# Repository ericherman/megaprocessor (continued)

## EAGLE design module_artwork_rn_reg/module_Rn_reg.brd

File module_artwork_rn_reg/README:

Rn Registers

This is where the General Purpose Registers (R0, R1, R2, R3) live. They
can be written to from various places.

Usually at most one register is written to in a cycle. However during
MUL and DIV upto all 4 may be written to in a cycle. In this mode each
register has its own shifter to generate its required new value.

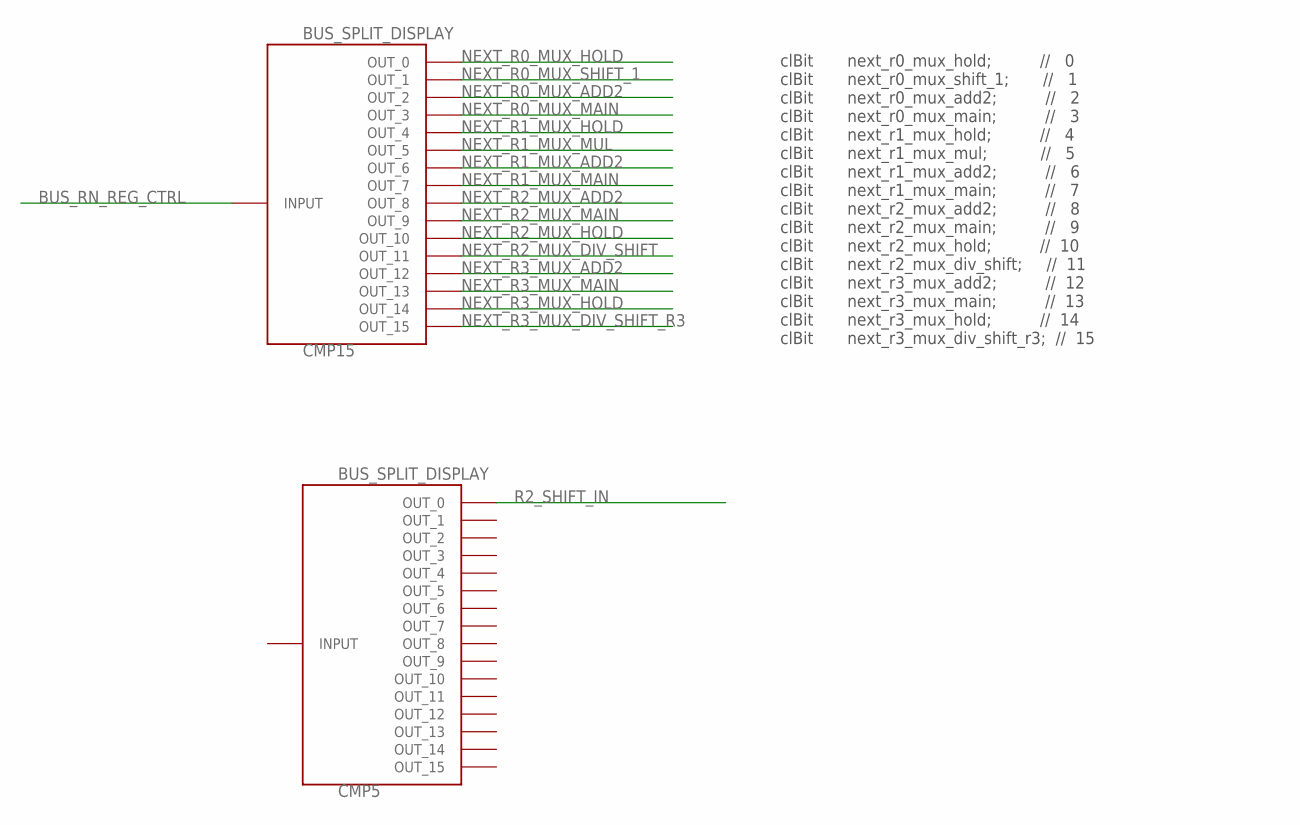
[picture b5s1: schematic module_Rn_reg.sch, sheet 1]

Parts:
CMP5, CMP15: BUS_SPLIT_DISPLAY

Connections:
BUS_RN_REG_CTRL: CMP15.INPUT
NEXT_R0_MUX_ADD2: CMP15.P$3 (OUT_2); also elsewhere on the board
NEXT_R0_MUX_HOLD: CMP15.P$1 (OUT_0); also elsewhere on the board
NEXT_R0_MUX_MAIN: CMP15.P$4 (OUT_3); also elsewhere on the board
NEXT_R0_MUX_SHIFT_1: CMP15.P$2 (OUT_1); also elsewhere on the board
NEXT_R1_MUX_ADD2: CMP15.P$7 (OUT_6); also elsewhere on the board
NEXT_R1_MUX_HOLD: CMP15.P$5 (OUT_4); also elsewhere on the board
NEXT_R1_MUX_MAIN: CMP15.P$8 (OUT_7); also elsewhere on the board
NEXT_R1_MUX_MUL: CMP15.P$6 (OUT_5); also elsewhere on the board
NEXT_R2_MUX_ADD2: CMP15.P$9 (OUT_8); also elsewhere on the board
NEXT_R2_MUX_DIV_SHIFT: CMP15.P$12 (OUT_11); also elsewhere on the board
NEXT_R2_MUX_HOLD: CMP15.P$11 (OUT_10); also elsewhere on the board
NEXT_R2_MUX_MAIN: CMP15.P$10 (OUT_9); also elsewhere on the board
NEXT_R3_MUX_ADD2: CMP15.P$13 (OUT_12); also elsewhere on the board
NEXT_R3_MUX_DIV_SHIFT_R3: CMP15.P$16 (OUT_15); also elsewhere on the board
NEXT_R3_MUX_HOLD: CMP15.P$15 (OUT_14); also elsewhere on the board
NEXT_R3_MUX_MAIN: CMP15.P$14 (OUT_13); also elsewhere on the board
R2_SHIFT_IN: CMP5.P$1 (OUT_0); also elsewhere on the board

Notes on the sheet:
clBit next_r0_mux_hold; // 0 clBit next_r0_mux_shift_1; // 1 clBit next_r0_mux_add2; // 2 clBit next_r0_mux_main; // 3 clBit next_r1_mux_hold; // 4 clBit next_r1_mux_mul; // 5 clBit next_r1_mux_add2; // 6 clBit next_r1_mux_main; // 7 clBit next_r2_mux_add2; // 8 clBit next_r2_mux_main; // 9 clBit n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

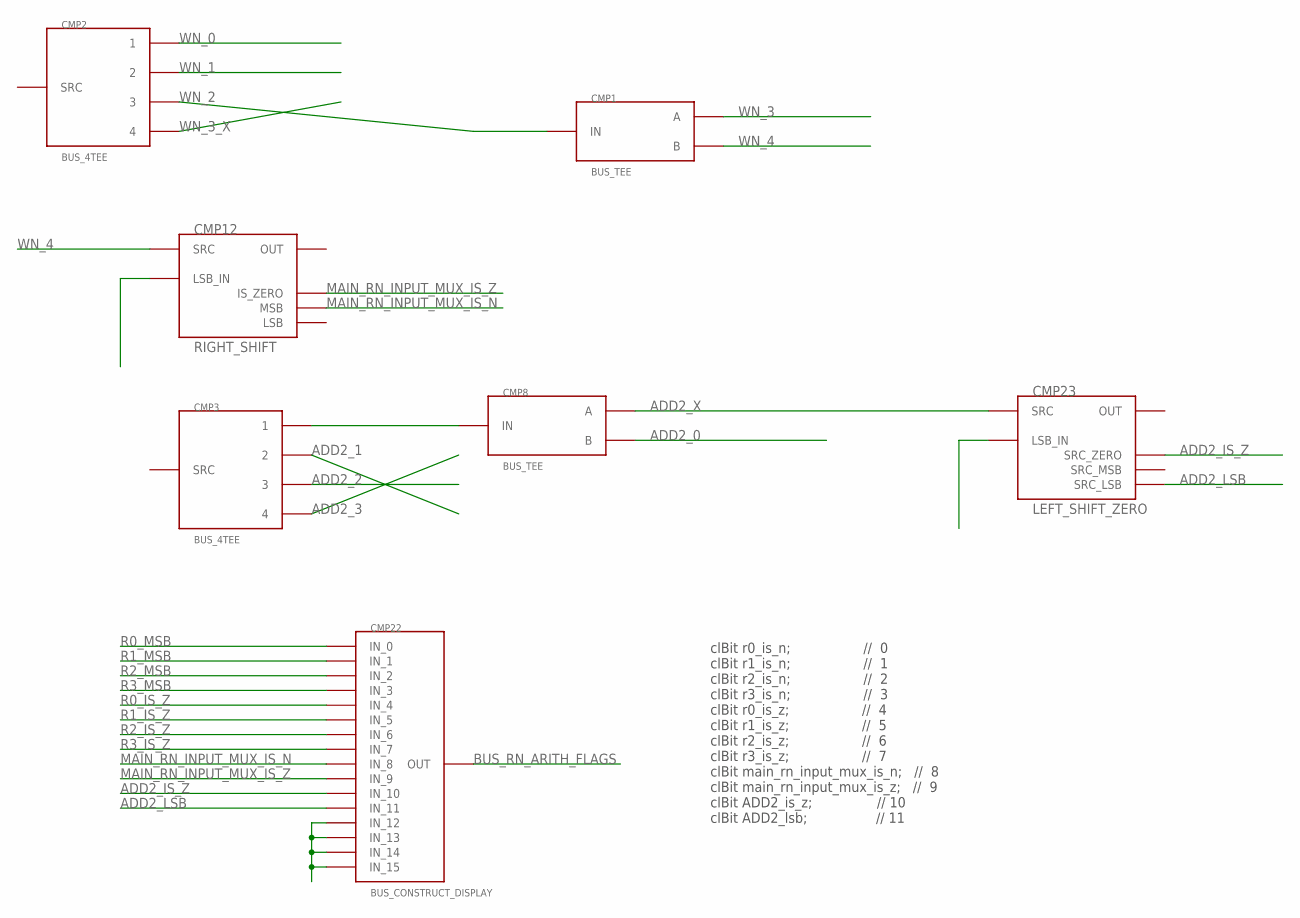
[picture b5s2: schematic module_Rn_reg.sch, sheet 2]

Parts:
CMP1, CMP8: BUS_TEE
CMP2, CMP3: BUS_4TEE
CMP12: RIGHT_SHIFT; SHIFT_ZERO
CMP22: BUS_CONSTRUCT_DISPLAY; BUS_SPLIT_DISPLAY
CMP23: LEFT_SHIFT_ZERO; SHIFT_ZERO

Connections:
ADD2_0: CMP8.OUTB (B); also elsewhere on the board
ADD2_1: CMP3.4; also elsewhere on the board
ADD2_2: CMP3.3; also elsewhere on the board
ADD2_3: CMP3.2; also elsewhere on the board
ADD2_IS_Z: CMP22.P$11 (IN_10), CMP23.IS_ZERO (SRC_ZERO)
ADD2_LSB: CMP22.P$12 (IN_11), CMP23.LSB (SRC_LSB)
ADD2_X: CMP8.OUT_A (A), CMP23.LSRC (SRC)
BUS_RN_ARITH_FLAGS: CMP22.INPUT (OUT)
MAIN_RN_INPUT_MUX_IS_N: CMP12.MSB, CMP22.P$9 (IN_8)
MAIN_RN_INPUT_MUX_IS_Z: CMP12.IS_ZERO, CMP22.P$10 (IN_9)
unnamed: CMP22.P$13 (IN_12), CMP22.P$14 (IN_13), CMP22.P$15 (IN_14), CMP22.P$16 (IN_15)
unnamed: CMP3.1, CMP8.INPUT (IN)
R0_IS_Z: CMP22.P$5 (IN_4); also elsewhere on the board
R0_MSB: CMP22.P$1 (IN_0); also elsewhere on the board
R1_IS_Z: CMP22.P$6 (IN_5); also elsewhere on the board
R1_MSB: CMP22.P$2 (IN_1); also elsewhere on the board
R2_IS_Z: CMP22.P$7 (IN_6); also elsewhere on the board
R2_MSB: CMP22.P$3 (IN_2); also elsewhere on the board
R3_IS_Z: CMP22.P$8 (IN_7); also elsewhere on the board
R3_MSB: CMP22.P$4 (IN_3); also elsewhere on the board
WN_0: CMP2.1; also elsewhere on the board
WN_1: CMP2.2; also elsewhere on the board
WN_2: CMP2.4; also elsewhere on the board
WN_3: CMP1.OUT_A (A); also elsewhere on the board
WN_3_X: CMP1.INPUT (IN), CMP2.3
WN_4: CMP1.OUTB (B), CMP12.RSRC (SRC)

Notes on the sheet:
clBit r0_is_n; // 0 clBit r1_is_n; // 1 clBit r2_is_n; // 2 clBit r3_is_n; // 3 clBit r0_is_z; // 4 clBit r1_is_z; // 5 clBit r2_is_z; // 6 clBit r3_is_z; // 7 clBit main_rn_input_mux_is_n; // 8 clBit main_rn_input_mux_is_z; // 9 clBit ADD2_is_z; // 10 clBit ADD2_lsb; // 11

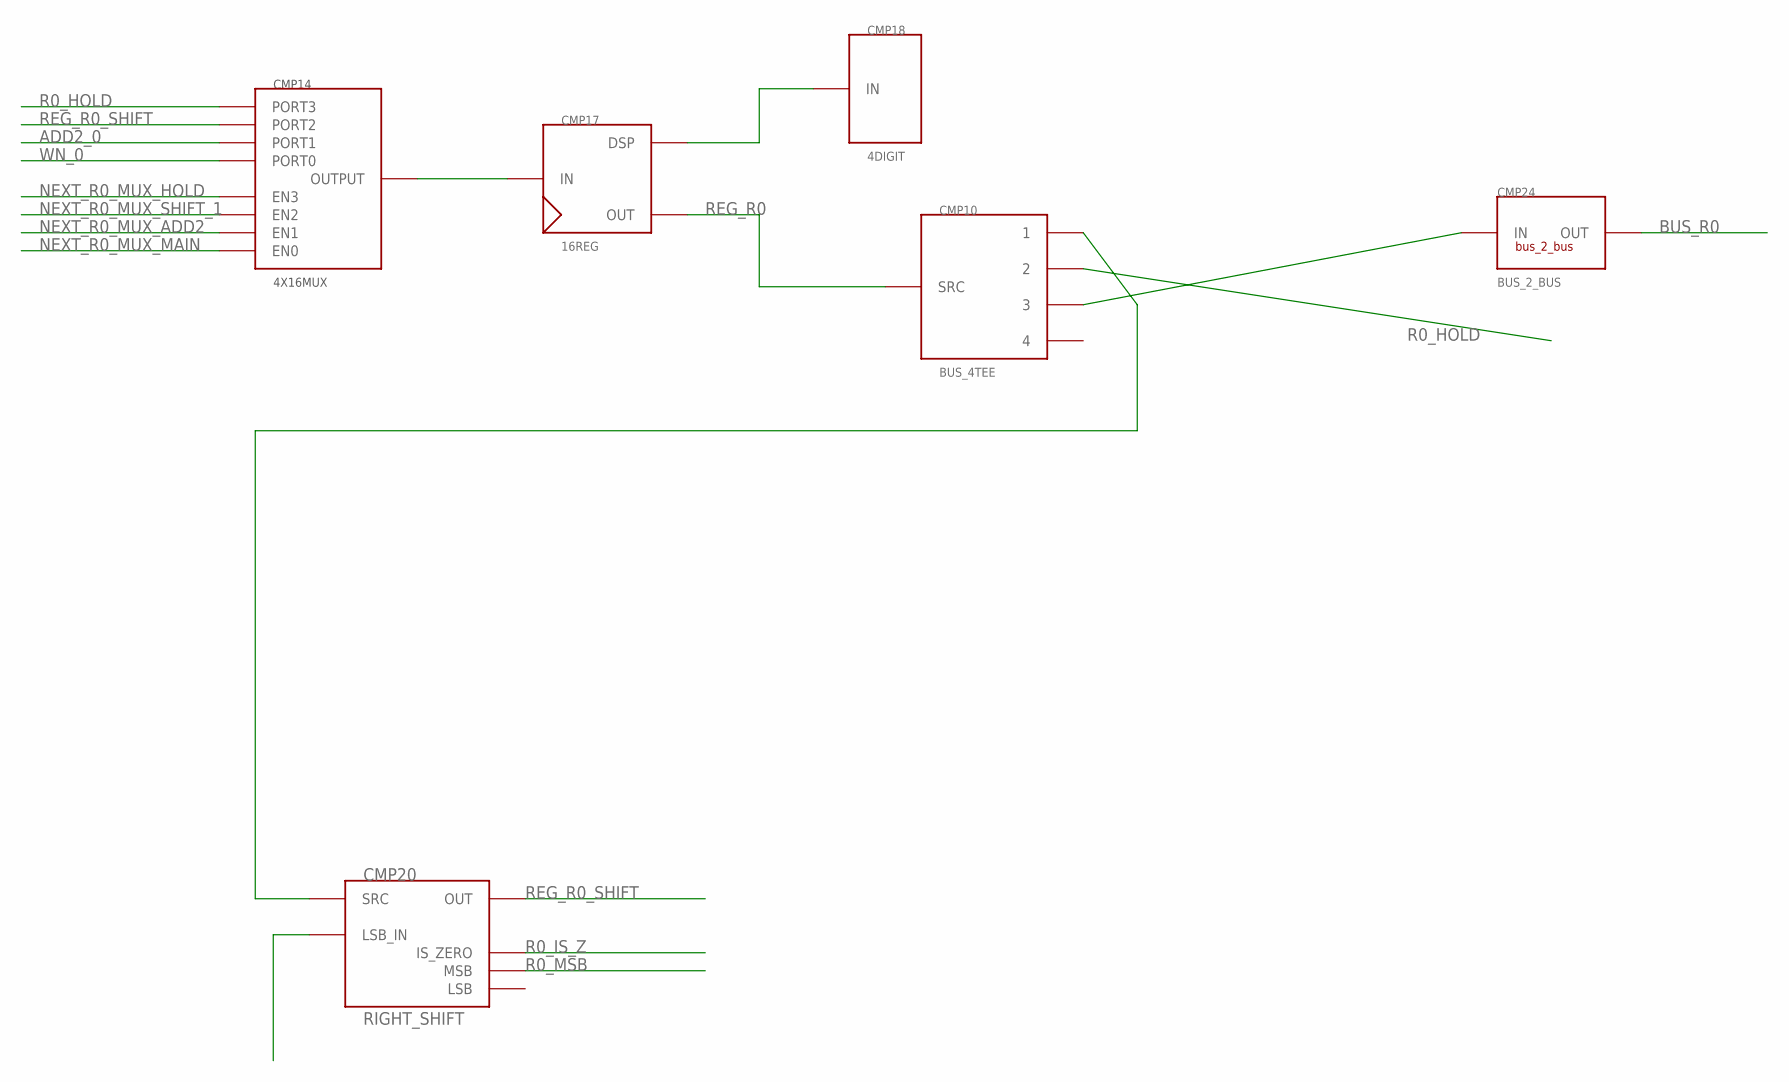
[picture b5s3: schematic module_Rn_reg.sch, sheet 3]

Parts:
CMP10: BUS_4TEE
CMP14: 4X16MUX
CMP17: 16REG
CMP18: 4DIGIT
CMP20: RIGHT_SHIFT; SHIFT_ZERO
CMP24: BUS_2_BUS; BUS2BUS

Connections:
ADD2_0: CMP14.PORT1; also elsewhere on the board
BUS_R0: CMP24.P$2 (OUT)
unnamed: CMP14.PORTOUT (OUTPUT), CMP17.INPUT (IN)
unnamed: CMP17.DISPLAY (DSP), CMP18.P$1
unnamed: CMP10.1, CMP20.RSRC (SRC)
unnamed: CMP10.3, CMP24.P$1 (IN)
NEXT_R0_MUX_ADD2: CMP14.EN1; also elsewhere on the board
NEXT_R0_MUX_HOLD: CMP14.EN3; also elsewhere on the board
NEXT_R0_MUX_MAIN: CMP14.EN0; also elsewhere on the board
NEXT_R0_MUX_SHIFT_1: CMP14.EN2; also elsewhere on the board
R0_HOLD: CMP10.2, CMP14.PORT3
R0_IS_Z: CMP20.IS_ZERO; also elsewhere on the board
R0_MSB: CMP20.MSB; also elsewhere on the board
REG_R0: CMP10.SRC, CMP17.OUT
REG_R0_SHIFT: CMP14.PORT2, CMP20.LSRC (OUT)
WN_0: CMP14.PORT0; also elsewhere on the board

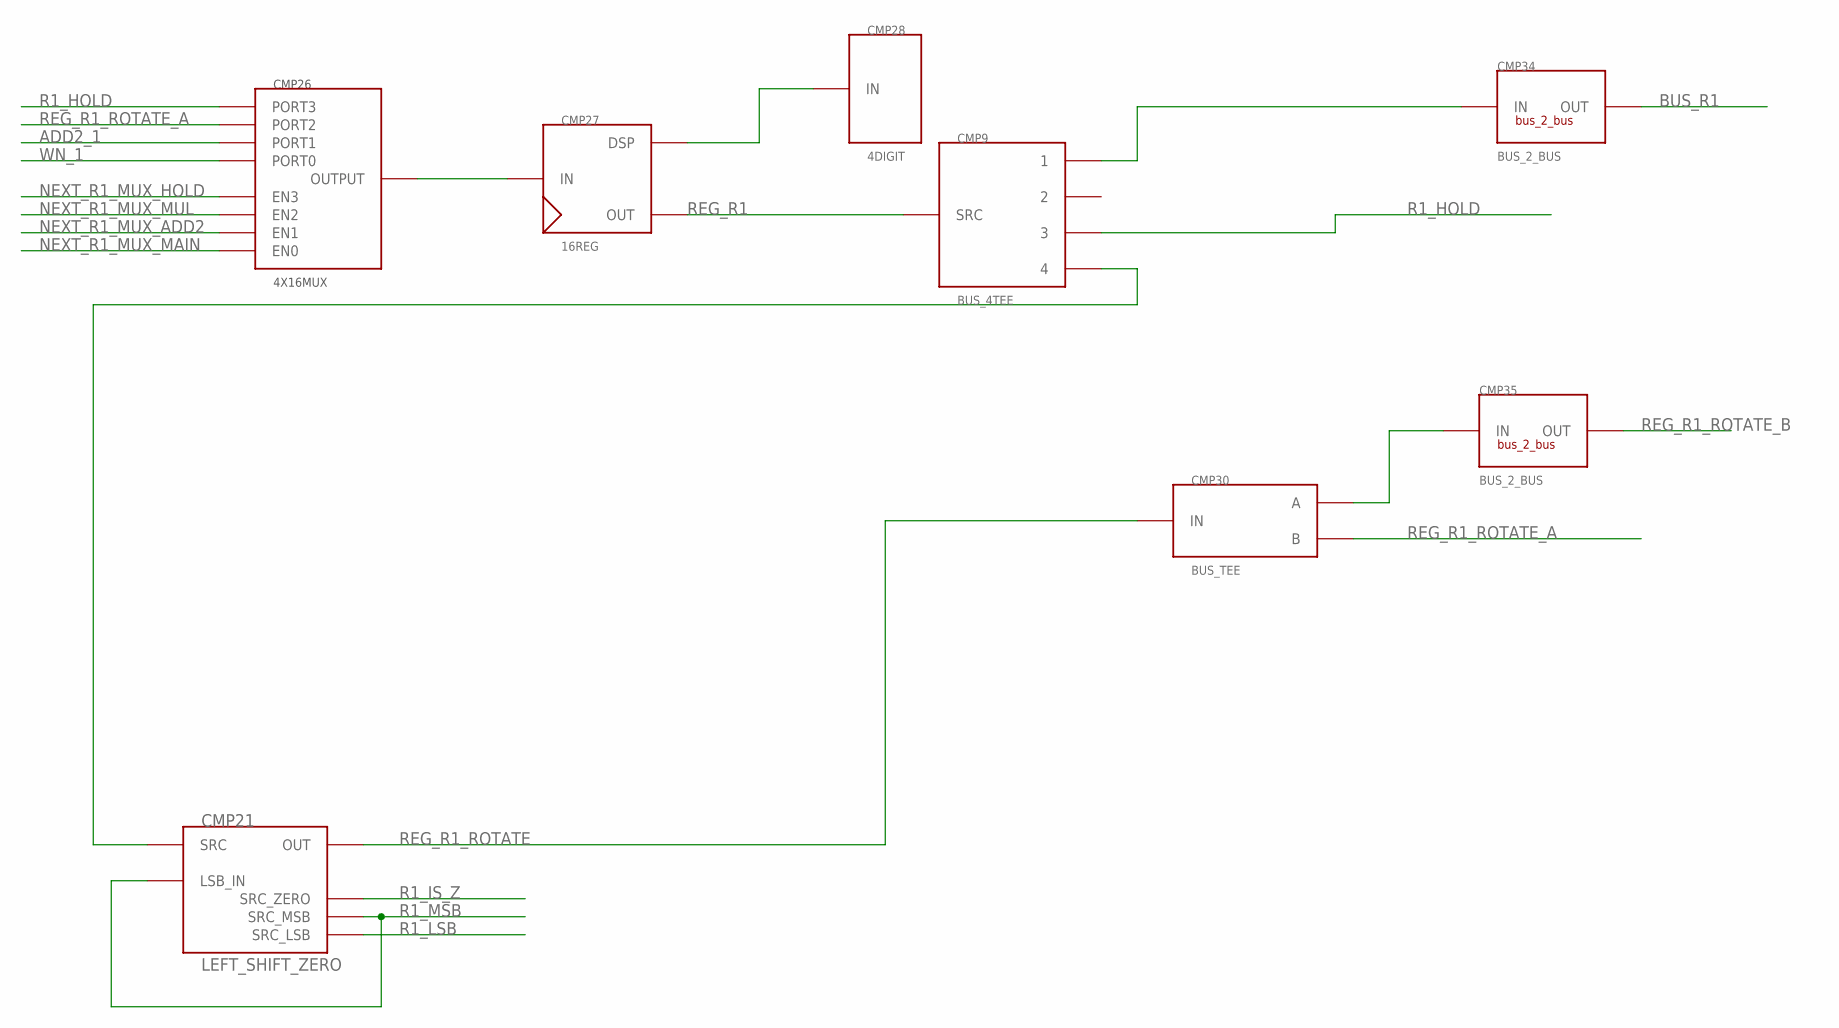
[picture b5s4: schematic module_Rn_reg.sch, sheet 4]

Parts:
CMP9: BUS_4TEE
CMP21: LEFT_SHIFT_ZERO; SHIFT_ZERO
CMP26: 4X16MUX
CMP27: 16REG
CMP28: 4DIGIT
CMP30: BUS_TEE
CMP34, CMP35: BUS_2_BUS; BUS2BUS

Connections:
ADD2_1: CMP26.PORT1; also elsewhere on the board
BUS_R1: CMP34.P$2 (OUT)
unnamed: CMP26.PORTOUT (OUTPUT), CMP27.INPUT (IN)
unnamed: CMP27.DISPLAY (DSP), CMP28.P$1
unnamed: CMP9.1, CMP34.P$1 (IN)
unnamed: CMP9.4, CMP21.LSRC (SRC)
unnamed: CMP30.OUT_A (A), CMP35.P$1 (IN)
NEXT_R1_MUX_ADD2: CMP26.EN1; also elsewhere on the board
NEXT_R1_MUX_HOLD: CMP26.EN3; also elsewhere on the board
NEXT_R1_MUX_MAIN: CMP26.EN0; also elsewhere on the board
NEXT_R1_MUX_MUL: CMP26.EN2; also elsewhere on the board
R1_HOLD: CMP9.3, CMP26.PORT3
R1_IS_Z: CMP21.IS_ZERO (SRC_ZERO); also elsewhere on the board
R1_LSB: CMP21.LSB (SRC_LSB)
R1_MSB: CMP21.MSB (SRC_MSB), CMP21.SHIFT_IN (LSB_IN); also elsewhere on the board
REG_R1: CMP9.SRC, CMP27.OUT
REG_R1_ROTATE: CMP21.RSRC (OUT), CMP30.INPUT (IN)
REG_R1_ROTATE_A: CMP26.PORT2, CMP30.OUTB (B)
REG_R1_ROTATE_B: CMP35.P$2 (OUT)
WN_1: CMP26.PORT0; also elsewhere on the board

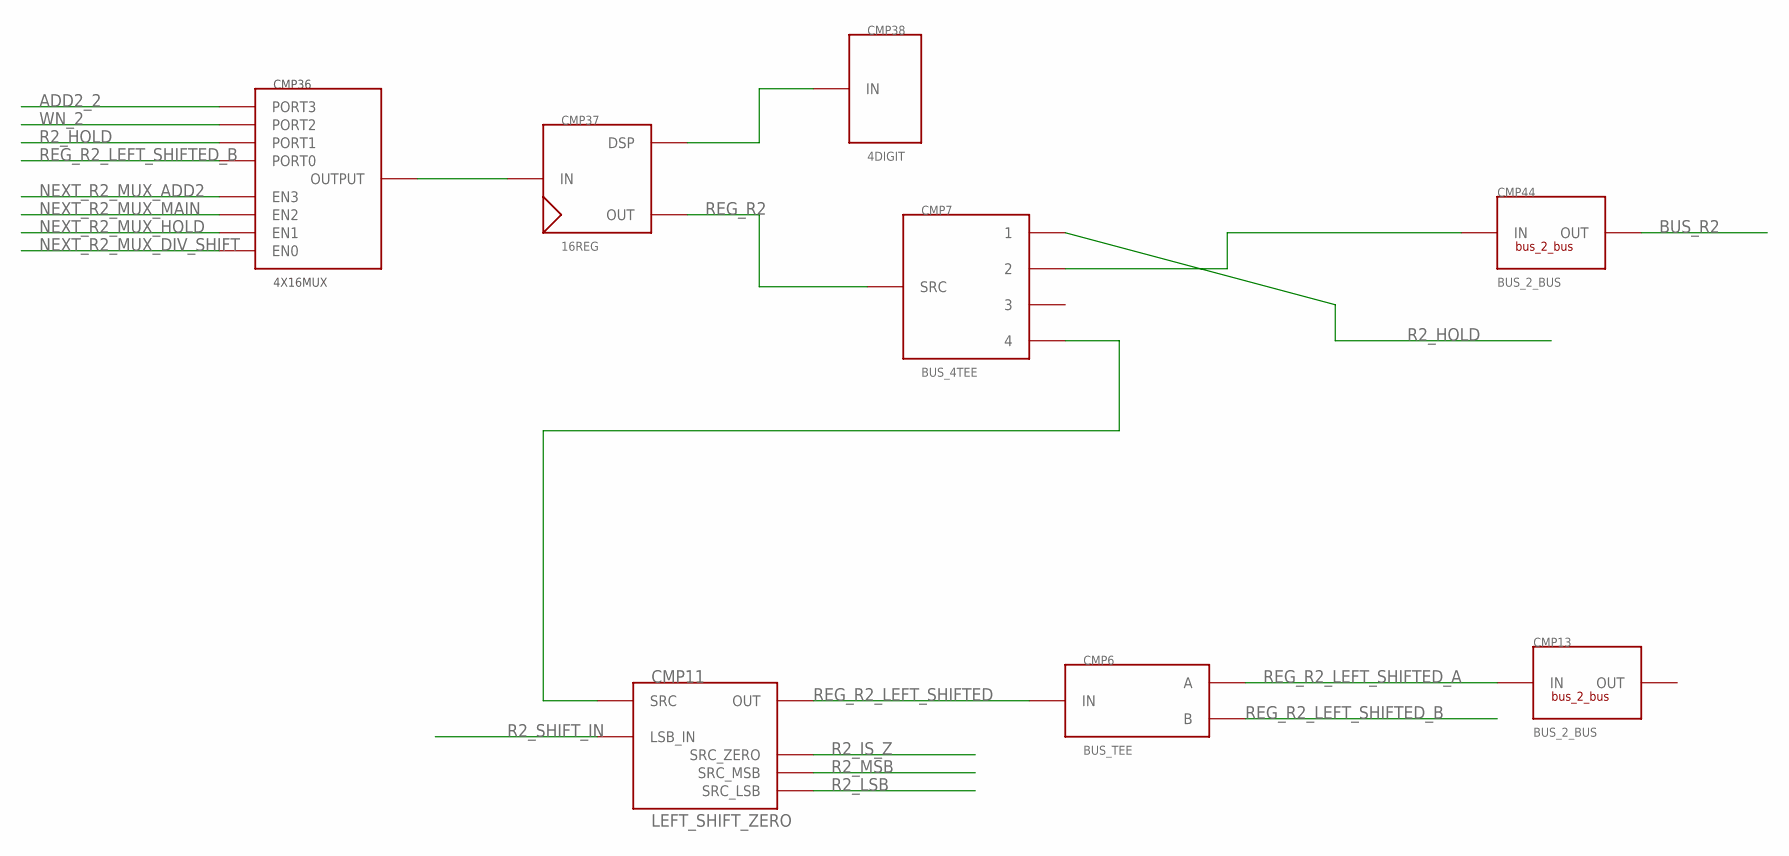
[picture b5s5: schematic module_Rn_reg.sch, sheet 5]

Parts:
CMP6: BUS_TEE
CMP7: BUS_4TEE
CMP11: LEFT_SHIFT_ZERO; SHIFT_ZERO
CMP13, CMP44: BUS_2_BUS; BUS2BUS
CMP36: 4X16MUX
CMP37: 16REG
CMP38: 4DIGIT

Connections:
ADD2_2: CMP36.PORT3; also elsewhere on the board
BUS_R2: CMP44.P$2 (OUT)
unnamed: CMP7.2, CMP44.P$1 (IN)
unnamed: CMP36.PORTOUT (OUTPUT), CMP37.INPUT (IN)
unnamed: CMP37.DISPLAY (DSP), CMP38.P$1
unnamed: CMP7.4, CMP11.LSRC (SRC)
NEXT_R2_MUX_ADD2: CMP36.EN3; also elsewhere on the board
NEXT_R2_MUX_DIV_SHIFT: CMP36.EN0; also elsewhere on the board
NEXT_R2_MUX_HOLD: CMP36.EN1; also elsewhere on the board
NEXT_R2_MUX_MAIN: CMP36.EN2; also elsewhere on the board
R2_HOLD: CMP7.1, CMP36.PORT1
R2_IS_Z: CMP11.IS_ZERO (SRC_ZERO); also elsewhere on the board
R2_LSB: CMP11.LSB (SRC_LSB)
R2_MSB: CMP11.MSB (SRC_MSB); also elsewhere on the board
R2_SHIFT_IN: CMP11.SHIFT_IN (LSB_IN); also elsewhere on the board
REG_R2: CMP7.SRC, CMP37.OUT
REG_R2_LEFT_SHIFTED: CMP6.INPUT (IN), CMP11.RSRC (OUT)
REG_R2_LEFT_SHIFTED_A: CMP6.OUT_A (A), CMP13.P$1 (IN)
REG_R2_LEFT_SHIFTED_B: CMP6.OUTB (B), CMP36.PORT0
WN_2: CMP36.PORT2; also elsewhere on the board

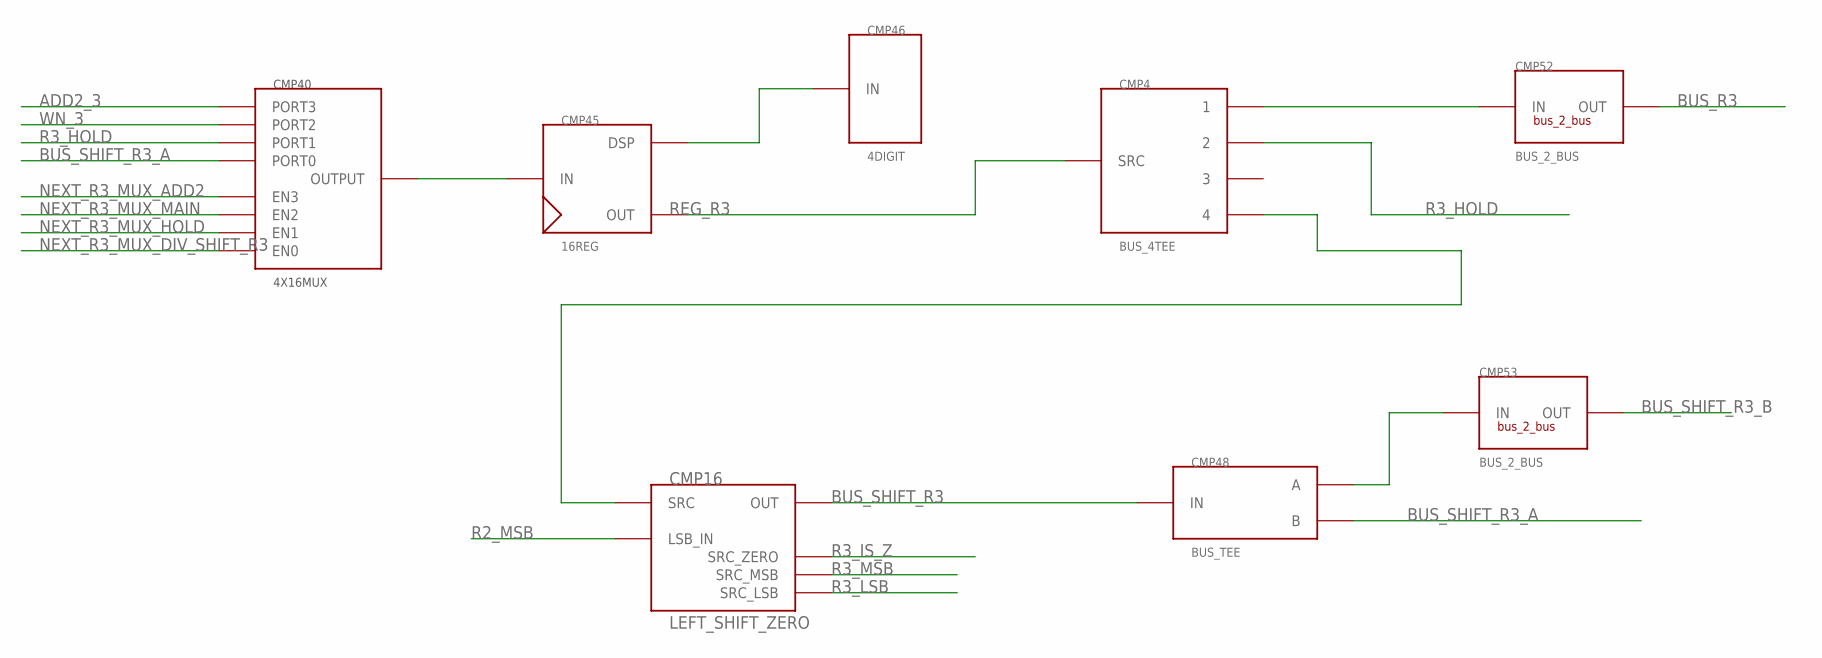
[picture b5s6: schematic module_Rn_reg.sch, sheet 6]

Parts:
CMP4: BUS_4TEE
CMP16: LEFT_SHIFT_ZERO; SHIFT_ZERO
CMP40: 4X16MUX
CMP45: 16REG
CMP46: 4DIGIT
CMP48: BUS_TEE
CMP52, CMP53: BUS_2_BUS; BUS2BUS

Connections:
ADD2_3: CMP40.PORT3; also elsewhere on the board
BUS_R3: CMP52.P$2 (OUT)
BUS_SHIFT_R3: CMP16.RSRC (OUT), CMP48.INPUT (IN)
BUS_SHIFT_R3_A: CMP40.PORT0, CMP48.OUTB (B)
BUS_SHIFT_R3_B: CMP53.P$2 (OUT)
unnamed: CMP4.1, CMP52.P$1 (IN)
unnamed: CMP40.PORTOUT (OUTPUT), CMP45.INPUT (IN)
unnamed: CMP45.DISPLAY (DSP), CMP46.P$1
unnamed: CMP4.4, CMP16.LSRC (SRC)
unnamed: CMP48.OUT_A (A), CMP53.P$1 (IN)
NEXT_R3_MUX_ADD2: CMP40.EN3; also elsewhere on the board
NEXT_R3_MUX_DIV_SHIFT_R3: CMP40.EN0; also elsewhere on the board
NEXT_R3_MUX_HOLD: CMP40.EN1; also elsewhere on the board
NEXT_R3_MUX_MAIN: CMP40.EN2; also elsewhere on the board
R2_MSB: CMP16.SHIFT_IN (LSB_IN); also elsewhere on the board
R3_HOLD: CMP4.2, CMP40.PORT1
R3_IS_Z: CMP16.IS_ZERO (SRC_ZERO); also elsewhere on the board
R3_LSB: CMP16.LSB (SRC_LSB)
R3_MSB: CMP16.MSB (SRC_MSB); also elsewhere on the board
REG_R3: CMP4.SRC, CMP45.OUT
WN_3: CMP40.PORT2; also elsewhere on the board

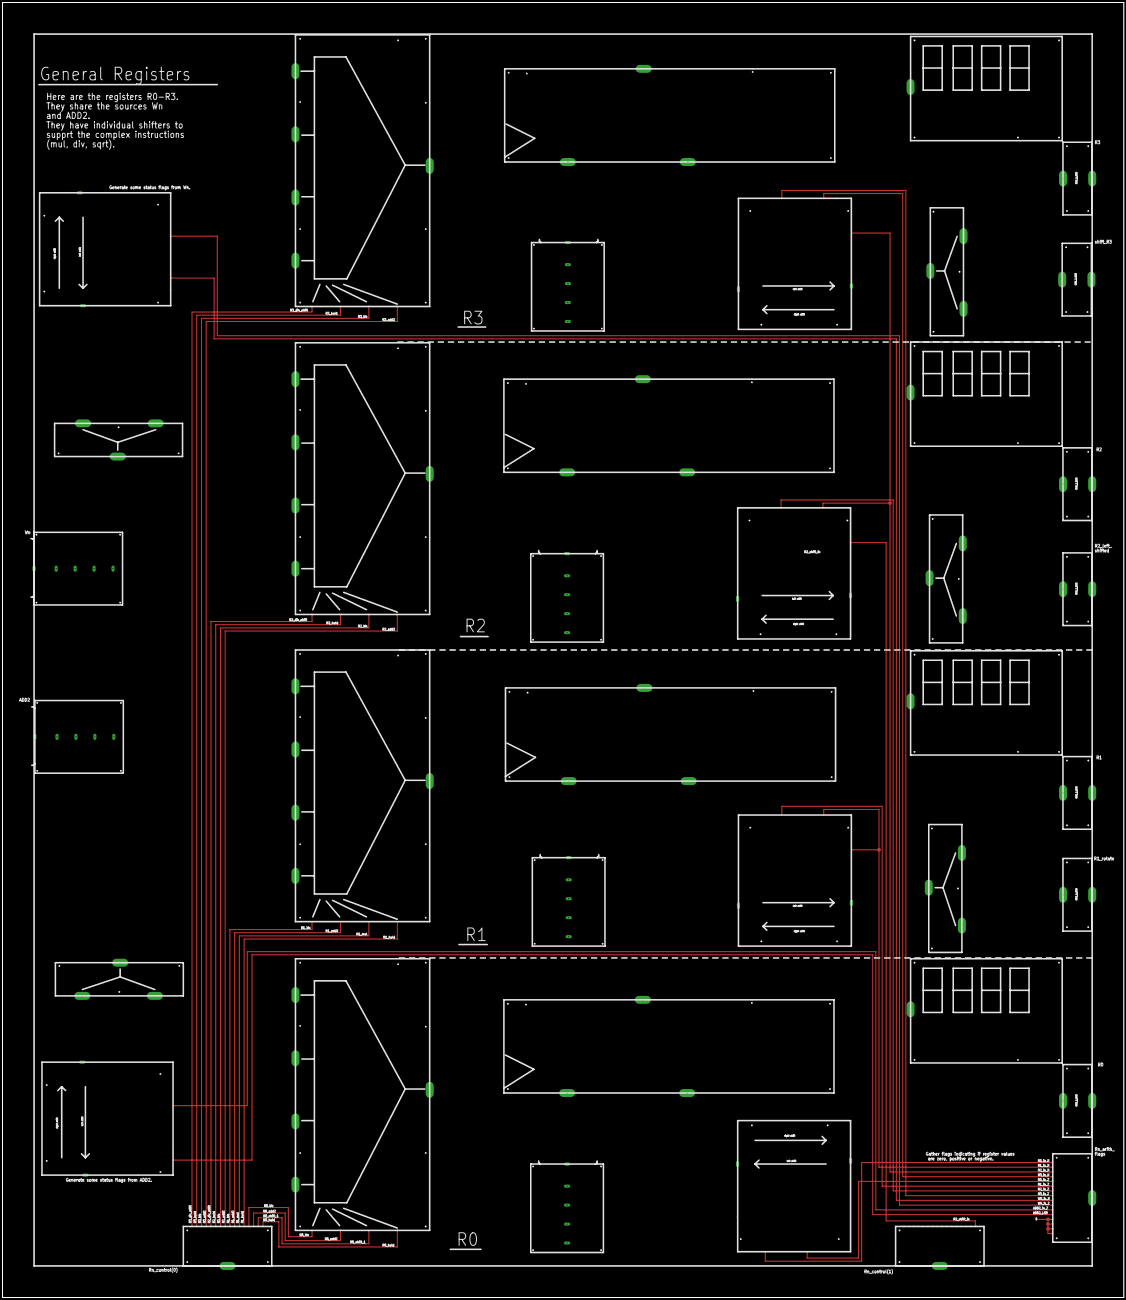
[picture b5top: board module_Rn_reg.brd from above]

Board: 2 copper layers, 901.7 x 1041.4 mm, 39 parts (0 on the bottom side), 76 nets.

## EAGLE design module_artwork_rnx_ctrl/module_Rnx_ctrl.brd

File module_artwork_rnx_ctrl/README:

Rnx Control

This generates the signals that control what the Rn Registers and Rx Mux
modules do each cycle. This depends on the current state and instruction
and uses signals generated by the decoder modules.

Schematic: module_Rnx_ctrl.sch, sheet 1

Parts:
CMP18, CMP87, CMP96: BUS_SPLIT_DISPLAY

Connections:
BUS_H_D1: CMP96.INPUT
BUS_PS: CMP87.INPUT
BUS_STATE: CMP18.INPUT
FLAG_C: CMP87.P$6 (OUT_5)
FLAG_D: CMP87.P$7 (OUT_6); also elsewhere on the board
FLAG_F0: CMP87.P$9 (OUT_8); also elsewhere on the board
FLAG_F1: CMP87.P$10 (OUT_9)
FLAG_F2: CMP87.P$11 (OUT_10)
FLAG_F3: CMP87.P$12 (OUT_11)
FLAG_F4: CMP87.P$13 (OUT_12)
FLAG_F5: CMP87.P$14 (OUT_13)
FLAG_I: CMP87.P$1 (OUT_0)
FLAG_N: CMP87.P$2 (OUT_1)
FLAG_V: CMP87.P$4 (OUT_3)
FLAG_X: CMP87.P$5 (OUT_4)
FLAG_Z: CMP87.P$3 (OUT_2)
H_0: CMP96.P$1 (OUT_0); also elsewhere on the board
H_1: CMP96.P$2 (OUT_1); also elsewhere on the board
H_2: CMP96.P$3 (OUT_2)
H_3: CMP96.P$4 (OUT_3)
H_4: CMP96.P$5 (OUT_4)
H_5: CMP96.P$6 (OUT_5)
H_6: CMP96.P$7 (OUT_6)
H_7: CMP96.P$8 (OUT_7)
H_8: CMP96.P$9 (OUT_8)
H_9: CMP96.P$10 (OUT_9)
H_10: CMP96.P$11 (OUT_10)
H_11: CMP96.P$12 (OUT_11)
H_12: CMP96.P$13 (OUT_12)
H_13: CMP96.P$14 (OUT_13)
H_14: CMP96.P$15 (OUT_14)
H_15: CMP96.P$16 (OUT_15)
STATE_0: CMP18.P$1 (OUT_0); also elsewhere on the board
STATE_1: CMP18.P$2 (OUT_1); also elsewhere on the board
STATE_2: CMP18.P$3 (OUT_2)
STATE_3: CMP18.P$4 (OUT_3); also elsewhere on the board
STATE_4: CMP18.P$5 (OUT_4); also elsewhere on the board
STATE_5: CMP18.P$6 (OUT_5); also elsewhere on the board
STATE_6: CMP18.P$7 (OUT_6); also elsewhere on the board
STATE_7: CMP18.P$8 (OUT_7); also elsewhere on the board
STATE_8: CMP18.P$9 (OUT_8); also elsewhere on the board
STATE_9: CMP18.P$10 (OUT_9)
STATE_10: CMP18.P$11 (OUT_10); also elsewhere on the board
STATE_11: CMP18.P$12 (OUT_11); also elsewhere on the board
STATE_12: CMP18.P$13 (OUT_12); also elsewhere on the board
STATE_13: CMP18.P$14 (OUT_13); also elsewhere on the board
STATE_14: CMP18.P$15 (OUT_14); also elsewhere on the board
STATE_15: CMP18.P$16 (OUT_15); also elsewhere on the board

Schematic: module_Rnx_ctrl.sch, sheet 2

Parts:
CMP86, CMP97: BUS_SPLIT_DISPLAY

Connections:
ADD1_RESULT_IS_N: CMP97.P$3 (OUT_2); also elsewhere on the board
ARITH_C: CMP97.P$2 (OUT_1); also elsewhere on the board
ARITH_V: CMP97.P$1 (OUT_0)
BIT_TEST_RESULT: CMP97.P$5 (OUT_4)
BUS_ALU_FLAGS: CMP97.INPUT
BUS_RN_ARITH_FLAGS: CMP86.INPUT
R0_IS_N: CMP86.P$1 (OUT_0)
R0_IS_Z: CMP86.P$5 (OUT_4)
R1_IS_N: CMP86.P$2 (OUT_1); also elsewhere on the board
R1_IS_Z: CMP86.P$6 (OUT_5)
R2_IS_N: CMP86.P$3 (OUT_2)
R2_IS_Z: CMP86.P$7 (OUT_6)
R3_IS_N: CMP86.P$4 (OUT_3)
R3_IS_Z: CMP86.P$8 (OUT_7); also elsewhere on the board
SHIFT_RESULT_C_FLAG: CMP97.P$4 (OUT_3)
SHIFT_RESULT_V_FLAG: CMP97.P$6 (OUT_5)

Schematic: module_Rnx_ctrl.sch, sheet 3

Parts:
CMP11, CMP57, CMP65: BUS_SPLIT_DISPLAY

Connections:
ALL_POPS: CMP57.P$1 (OUT_0); also elsewhere on the board
BUS_DECODE_RNX_1: CMP57.INPUT
BUS_INSTR: CMP11.INPUT
DIV_BY_ZERO_N: CMP65.P$9 (OUT_8); also elsewhere on the board
DIV_DIFF_SIGN: CMP65.P$13 (OUT_12); also elsewhere on the board
INSTR_0: CMP11.P$1 (OUT_0); also elsewhere on the board
INSTR_0_N: CMP11.P$9 (OUT_8); also elsewhere on the board
INSTR_1: CMP11.P$2 (OUT_1); also elsewhere on the board
INSTR_1_N: CMP11.P$10 (OUT_9); also elsewhere on the board
INSTR_2: CMP11.P$3 (OUT_2); also elsewhere on the board
INSTR_2_N: CMP11.P$11 (OUT_10); also elsewhere on the board
INSTR_3: CMP11.P$4 (OUT_3); also elsewhere on the board
INSTR_4: CMP11.P$5 (OUT_4)
INSTR_5: CMP11.P$6 (OUT_5)
INSTR_6: CMP11.P$7 (OUT_6)
INSTR_6_N: CMP11.P$15 (OUT_14); also elsewhere on the board
INSTR_7: CMP11.P$8 (OUT_7); also elsewhere on the board
INSTR_7_N: CMP11.P$16 (OUT_15); also elsewhere on the board
IS_END_N: CMP57.P$14 (OUT_13); also elsewhere on the board
LOAD_WEIGHT: CMP65.P$14 (OUT_13); also elsewhere on the board
OPCODE_IS_ADDX: CMP57.P$3 (OUT_2); also elsewhere on the board
OPCODE_IS_ADD_SP_STATE_2: CMP57.P$8 (OUT_7); also elsewhere on the board
OPCODE_IS_DIV: CMP65.P$6 (OUT_5); also elsewhere on the board
OPCODE_IS_DIVS_STATE_0: CMP57.P$16 (OUT_15); also elsewhere on the board
OPCODE_IS_DIV_STATE_0: CMP65.P$10 (OUT_9); also elsewhere on the board
OPCODE_IS_INDIRECT_POSTINC: CMP65.P$1 (OUT_0); also elsewhere on the board
OPCODE_IS_JSR_ABS: CMP57.P$15 (OUT_14); also elsewhere on the board
OPCODE_IS_JSR_R0: CMP65.P$3 (OUT_2); also elsewhere on the board
OPCODE_IS_LDI_X: CMP65.P$11 (OUT_10); also elsewhere on the board
OPCODE_IS_LD_ST: CMP65.P$4 (OUT_3); also elsewhere on the board
OPCODE_IS_MOVE_R0_SP_STATE_0: CMP57.P$9 (OUT_8); also elsewhere on the board
OPCODE_IS_MUL: CMP57.P$10 (OUT_9); also elsewhere on the board
OPCODE_IS_MULS: CMP57.P$5 (OUT_4); also elsewhere on the board
OPCODE_IS_NEGX: CMP57.P$6 (OUT_5); also elsewhere on the board
OPCODE_IS_POP_PS: CMP65.P$5 (OUT_4); also elsewhere on the board
OPCODE_IS_POSTINC_GROUP: CMP65.P$15 (OUT_14); also elsewhere on the board
OPCODE_IS_SHIFT_BIT: CMP57.P$4 (OUT_3); also elsewhere on the board
OPCODE_IS_SQRT: CMP57.P$12 (OUT_11); also elsewhere on the board
OPCODE_IS_STACK_GROUP: CMP57.P$13 (OUT_12); also elsewhere on the board
OPCODE_IS_STACK_REL_STATE_2: CMP57.P$11 (OUT_10); also elsewhere on the board
OPCODE_IS_SUBX: CMP57.P$2 (OUT_1); also elsewhere on the board
OPCODE_IS_SXT: CMP57.P$7 (OUT_6); also elsewhere on the board
OPCODE_IS_TRAP: CMP65.P$2 (OUT_1); also elsewhere on the board
OPCODE_IS_X_ARITH: CMP65.P$16 (OUT_15); also elsewhere on the board
SHIFT_IS_SHIFTING: CMP65.P$8 (OUT_7); also elsewhere on the board
WR_RN_USING_RA__BIT: CMP65.P$7 (OUT_6); also elsewhere on the board
WR_RN_USING_RA__REG_REG_EXCEPTIONS_N: CMP65.P$12 (OUT_11); also elsewhere on the board

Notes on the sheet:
clBit all_pops; // 0 clBit opcode_is_subx; // 1 clBit opcode_is_addx; // 2 clBit opcode_is_shift_bit; // 3 clBit opcode_is_muls; // 4 clBit opcode_is_negx; // 5 clBit opcode_is_sxt; // 6 clBit opcode_is_add_sp_state_2; // 7 clBit opcode_is_move_r0_sp_state_0; // 8 clBit opcode_is_mul; // 9 clBit op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
clBit opcode_is_indirect_postinc; // 0 clBit opcode_is_trap; // 1 clBit opcode_is_jsr_r0; // 2 clBit opcode_is_ld_st; // 3 clBit opcode_is_pop_ps; // 4 clBit opcode_is_div; // 5 clBit wr_RN_using_ra__bit; // 6 clBit shift_is_shifting; // 7 clBit div_by_zero_n; // 8 clBit opcode_is_div_state_0; // 9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

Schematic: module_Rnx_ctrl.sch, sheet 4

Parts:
CMP25, CMP89, CMP99: BUS_CONSTRUCT_DISPLAY; BUS_SPLIT_DISPLAY

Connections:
ADD2_X_MUX_RI__SP: CMP25.P$8 (IN_7); also elsewhere on the board
BUS_RX_MUX_CTRL: CMP25.INPUT (OUT)
MAIN_RN_INPUT_MUX_0XT_READ: CMP25.P$2 (IN_1); also elsewhere on the board
MAIN_RN_INPUT_MUX_ALU: CMP25.P$1 (IN_0); also elsewhere on the board
MAIN_RN_INPUT_MUX_SHIFT_RAC: CMP25.P$3 (IN_2); also elsewhere on the board
unnamed: CMP89.P$2 (IN_1), CMP89.P$3 (IN_2), CMP89.P$4 (IN_3), CMP89.P$5 (IN_4), CMP89.P$6 (IN_5), CMP89.P$7 (IN_6), CMP89.P$8 (IN_7), CMP89.P$9 (IN_8), CMP89.P$10 (IN_9), CMP89.P$11 (IN_10), CMP89.P$12 (IN_11), CMP89.P$13 (IN_12), CMP89.P$14 (IN_13), CMP89.P$15 (IN_14), CMP89.P$16 (IN_15)
NEXT_R0_MUX_ADD2: CMP99.P$3 (IN_2); also elsewhere on the board
NEXT_R0_MUX_HOLD: CMP99.P$1 (IN_0); also elsewhere on the board
NEXT_R0_MUX_MAIN: CMP99.P$4 (IN_3); also elsewhere on the board
NEXT_R1_MUX_ADD2: CMP99.P$7 (IN_6); also elsewhere on the board
NEXT_R1_MUX_HOLD: CMP99.P$5 (IN_4); also elsewhere on the board
NEXT_R1_MUX_MAIN: CMP99.P$8 (IN_7); also elsewhere on the board
NEXT_R2_MUX_ADD2: CMP99.P$9 (IN_8); also elsewhere on the board
NEXT_R2_MUX_HOLD: CMP99.P$12 (IN_11); also elsewhere on the board
NEXT_R2_MUX_MAIN: CMP99.P$10 (IN_9); also elsewhere on the board
NEXT_R3_MUX_ADD2: CMP99.P$13 (IN_12); also elsewhere on the board
NEXT_R3_MUX_DIV_SHIFT_R3: CMP99.P$16 (IN_15); also elsewhere on the board
NEXT_R3_MUX_HOLD: CMP99.P$15 (IN_14); also elsewhere on the board
NEXT_R3_MUX_MAIN: CMP99.P$14 (IN_13); also elsewhere on the board
OPCODE_IS_SXT: CMP25.P$4 (IN_3); also elsewhere on the board
R2_SHIFT_IN: CMP89.P$1 (IN_0); also elsewhere on the board
RAC_MUX_0: CMP25.P$13 (IN_12); also elsewhere on the board
RAC_MUX_1: CMP25.P$14 (IN_13); also elsewhere on the board
RAC_MUX_3: CMP25.P$16 (IN_15); also elsewhere on the board
RA_NORM_2: CMP25.P$15 (IN_14); also elsewhere on the board
RB_MUX_0: CMP25.P$9 (IN_8); also elsewhere on the board
RB_MUX_1: CMP25.P$10 (IN_9); also elsewhere on the board
RB_MUX_2: CMP25.P$11 (IN_10); also elsewhere on the board
RB_MUX_3: CMP25.P$12 (IN_11); also elsewhere on the board
RI_MUX_2_QUAL: CMP25.P$5 (IN_4); also elsewhere on the board
RI_MUX_3_QUAL: CMP25.P$6 (IN_5); also elsewhere on the board
RI_MUX_H: CMP25.P$7 (IN_6); also elsewhere on the board
SQRT_STATE_10_EVEN_CYCLE: CMP99.P$2 (IN_1); also elsewhere on the board
STATE_11: CMP99.P$11 (IN_10); also elsewhere on the board
STATE_13: CMP99.P$6 (IN_5); also elsewhere on the board

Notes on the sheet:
clBit next_r0_mux_hold; // 0 clBit next_r0_mux_shift_1; // 1 clBit next_r0_mux_add2; // 2 clBit next_r0_mux_main; // 3 clBit next_r1_mux_hold; // 4 clBit next_r1_mux_mul; // 5 clBit next_r1_mux_add2; // 6 clBit next_r1_mux_main; // 7 clBit next_r2_mux_add2; // 8 clBit next_r2_mux_main; // 9 clBit n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
clBit main_rn_input_mux_alu; // 0 clBit main_rn_input_mux_0xt_read; // 1 clBit main_rn_input_mux_shift_rac; // 2 clBit main_rn_input_mux_sxt; // 3 clBit RI_mux_2; // 4 clBit RI_mux_3; // 5 clBit RI_mux_H; // 6 clBit RI_mux_SP; // 7 clBit RB_mux_0; // 8 clBit RB_mux_1; // 9 clBit RB_mux_2; // 10 clB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

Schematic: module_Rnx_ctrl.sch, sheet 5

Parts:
CMP52: BUS_CONSTRUCT_DISPLAY; BUS_SPLIT_DISPLAY

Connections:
ADD2_X_MUX_RI__H: CMP52.P$1 (IN_0); also elsewhere on the board
ADD2_X_MUX_RI__SP: CMP52.P$3 (IN_2); also elsewhere on the board
ADD2_X_MUX_RI__SP__JSR_ABS: CMP52.P$2 (IN_1); also elsewhere on the board
ADDER_X_MUX_SPECIAL: CMP52.P$5 (IN_4); also elsewhere on the board
ADDER_Y_MUX_SPECIAL: CMP52.P$6 (IN_5); also elsewhere on the board
unnamed: CMP52.P$7 (IN_6), CMP52.P$8 (IN_7), CMP52.P$9 (IN_8), CMP52.P$10 (IN_9), CMP52.P$11 (IN_10), CMP52.P$12 (IN_11), CMP52.P$13 (IN_12), CMP52.P$14 (IN_13), CMP52.P$15 (IN_14), CMP52.P$16 (IN_15)
NEXT_ADDR_MUX_RI__SP: CMP52.P$4 (IN_3); also elsewhere on the board
RNX_SPECIALS: CMP52.INPUT (OUT)

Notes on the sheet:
clBit add2_x_mux_ri__h; // 0 clBit add2_x_mux_ri__sp__jsr_abs; // 1 clBit add2_x_mux_ri__sp; // 2 clBit next_addr_mux_ri__sp; // 3 clBit adder_x_special; // 4 clBit adder_y_special; // 5

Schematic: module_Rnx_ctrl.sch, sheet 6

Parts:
CMP38, CMP39, CMP51, CMP88: DECODER4

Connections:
DIR_SZ_IS_LOAD_BYTE: CMP88.P1; also elsewhere on the board
DIR_SZ_IS_LOAD_WORD: CMP88.P0; also elsewhere on the board
H_0: CMP39.A0; also elsewhere on the board
H_1: CMP39.A1; also elsewhere on the board
INSTR_0: CMP51.A0; also elsewhere on the board
INSTR_1: CMP51.A1; also elsewhere on the board
INSTR_2: CMP38.A0, CMP88.A0; also elsewhere on the board
INSTR_3: CMP38.A1, CMP88.A1; also elsewhere on the board
OPCODE_IS_SHIFT_BIT: CMP39.E; also elsewhere on the board
RA_MUX_NORM_EN: CMP51.E; also elsewhere on the board
RA_NORM_0: CMP51.P0; also elsewhere on the board
RA_NORM_1: CMP51.P1; also elsewhere on the board
RA_NORM_2: CMP51.P2; also elsewhere on the board
RA_NORM_3: CMP51.P3; also elsewhere on the board
RB_MUX_NORM_EN: CMP38.E; also elsewhere on the board
RB_NORM_0: CMP38.P0; also elsewhere on the board
RB_NORM_1: CMP38.P1; also elsewhere on the board
RB_NORM_2: CMP38.P2; also elsewhere on the board
RB_NORM_3: CMP38.P3; also elsewhere on the board
RB_SHIFT_0: CMP39.P0; also elsewhere on the board
RB_SHIFT_1: CMP39.P1; also elsewhere on the board
RB_SHIFT_2: CMP39.P2; also elsewhere on the board
RB_SHIFT_3: CMP39.P3; also elsewhere on the board

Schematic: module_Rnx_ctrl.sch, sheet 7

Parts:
CMP21, CMP23: 2AND
CMP31, CMP90: 1BUF
CMP47: 2OR
CMP53: 3AND

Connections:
DIV_SGN_STATE12_NZ_REM: CMP53.OUT_P; also elsewhere on the board
FLAG_F0: CMP53.P$3 (3); also elsewhere on the board
H_0: CMP31.IN; also elsewhere on the board
H_0_N: CMP23.P$1 (1), CMP31.N
IS_STATE_4_6: CMP47.OUT_P; also elsewhere on the board
OPCODE_IS_SQRT: CMP21.P$1 (1); also elsewhere on the board
R3_IS_NZ: CMP53.P$1 (1), CMP90.N
R3_IS_Z: CMP90.IN; also elsewhere on the board
SQRT_STATE_0: CMP21.OUT_P; also elsewhere on the board
SQRT_STATE_10_EVEN_CYCLE: CMP23.OUT_P; also elsewhere on the board
STATE_0: CMP21.P$2 (2); also elsewhere on the board
STATE_4: CMP47.P$1 (A2); also elsewhere on the board
STATE_6: CMP47.P$2 (A1); also elsewhere on the board
STATE_10: CMP23.P$2 (2); also elsewhere on the board
STATE_12: CMP53.P$2 (2); also elsewhere on the board

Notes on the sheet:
RC_bit = bus_f_instr.instr[0]; is_simple_reg_to_reg = ~bus_f_instr.instr[7]; RI_bit = bus_f_instr.instr[1]; sz_bit = bus_f_instr.instr[2]; size_bit_is_byte = sz_bit;
is_state_4_6 = Cpnt_2OR(bus_state[4],bus_state[6]);
sqrt_state_10_even_cycle = Cpnt_2AND(bus_state[10], ~bus_H[0]);
sqrt_state_0 = Cpnt_2AND(bus_decode_rnx_1.opcode_is_sqrt, bus_state[0]);
div_sgn_state12_nz_rem = Cpnt_3AND(bus_state[12], bus_PS[WiC_PS_FLAG_INDEX_F0], ~bus_rn_arith_flags.r3_is_z);

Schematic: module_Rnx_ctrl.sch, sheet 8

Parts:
CMP67, CMP76, CMP84: 2AND

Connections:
ADDER_X_MUX_R1__DIV: CMP67.OUT_P; also elsewhere on the board
ADDER_Y_MUX_R2__DIV: CMP76.OUT_P; also elsewhere on the board
FLAG_D: CMP67.P$1 (1); also elsewhere on the board
NEXT_R1_MUX_MAIN__DIV: CMP84.OUT_P; also elsewhere on the board
OPCODE_IS_DIV: CMP76.P$2 (2); also elsewhere on the board
OPCODE_IS_DIVS_STATE_0: CMP84.P$2 (2); also elsewhere on the board
R1_IS_N: CMP84.P$1 (1); also elsewhere on the board
STATE_3: CMP76.P$1 (1); also elsewhere on the board
STATE_12: CMP67.P$2 (2); also elsewhere on the board

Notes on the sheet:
adder_x_mux_r1__div = Cpnt_2AND(bus_state[12], bus_PS[WiC_PS_FLAG_INDEX_D]);
adder_y_mux_r1__div = bus_decode_rnx_2.opcode_is_divs_state_0;
adder_y_mux_r2__div = Cpnt_2AND(bus_decode_rnx_2.opcode_is_div, bus_state[3]);
adder_y_mux_r3__div = bus_state[12];
next_r1_mux_main__div = Cpnt_2AND(bus_decode_rnx_2.opcode_is_divs_state_0, bus_rn_arith_flags.r1_is_n);
